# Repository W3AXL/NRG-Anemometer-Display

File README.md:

# NRG Anemometer Display
A compact, cheap interface unit for NRG #40C 3-cup anemometers.

This project started because I found a great deal on some NRG anemometers on eBay. Two for $40 was hard to turn down, especially because each unit is calibrated from the factory and said calibration is freely available on [NRG's website](https://www.nrgsystems.com/support/product-support/calibration-reports/).

The heavy lifting of the circuit was already done for me - the technical whitepaper from NRG clearly illustrates an almost-complete schematic. The only real work to be done was selection of components, the MCU interfacing, and board design for a nice compact meter.

I went through a lot of initial brainstorming for the interface concept - battery powered, or DC? Integrated data logging, or keep it simple? How many buttons? Should it beep at you annoyingly?

In the end, a dead-simple interface showing current and maximum wind readings was decided on. Power is provivded via a micro-USB plug, which also creates a serial port for real-time data transfer to a PC. The display is your standard run-of-the-mill eBay 1.3" OLED display, driven by I2C, and available for a few dollars all over the place. Boards were designed in Kicad and manufactured by JLCPCB. Components were sourced from Digikey, and the whole thing took a couple days to get working.

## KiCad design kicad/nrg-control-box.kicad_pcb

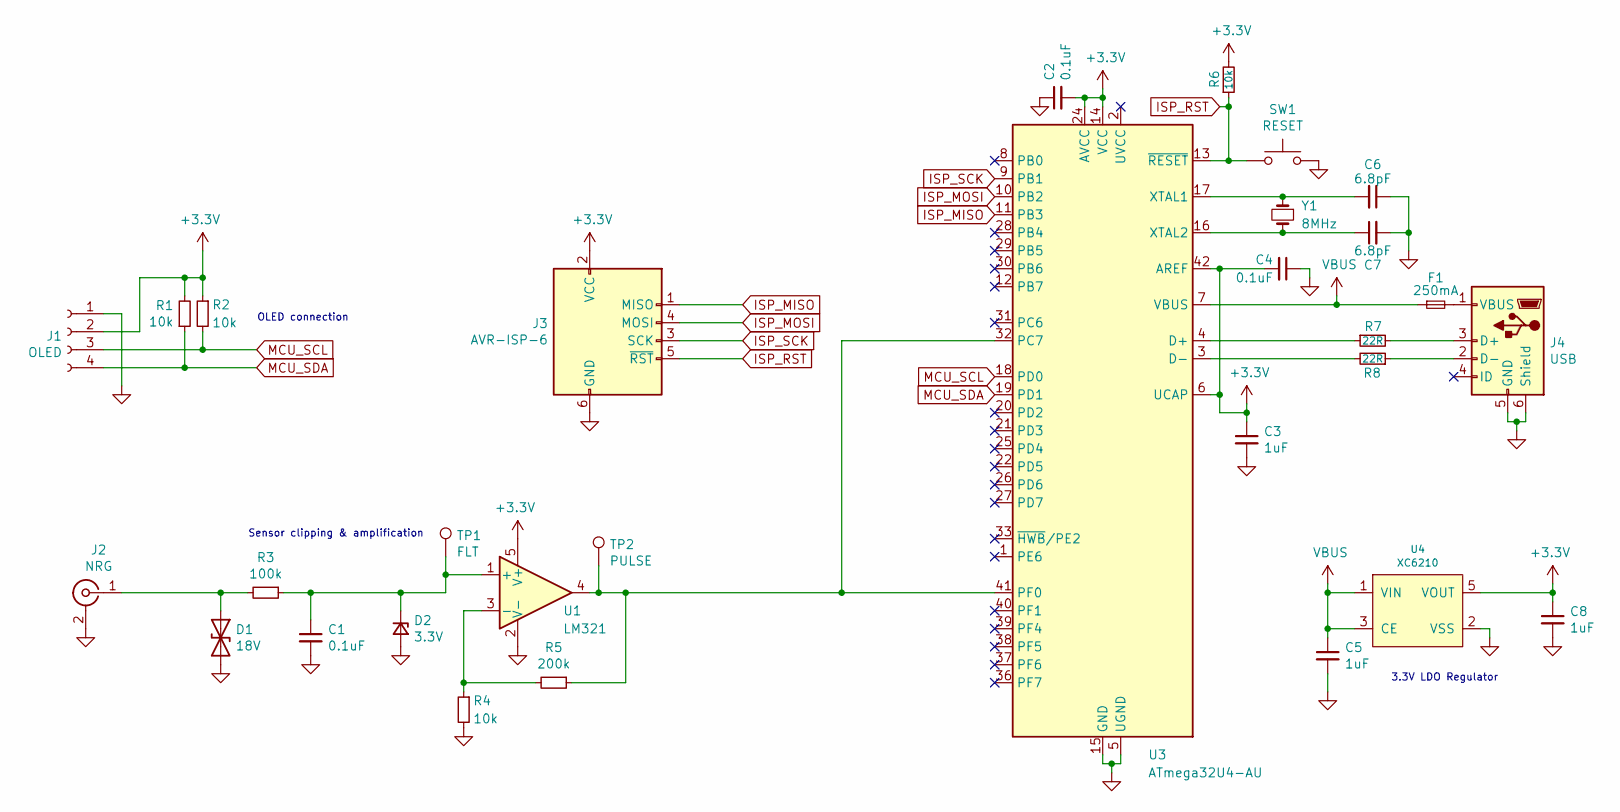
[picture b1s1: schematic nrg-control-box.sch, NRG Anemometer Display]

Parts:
C1, C2, C4: 0.1uF; C_0805_2012Metric_Pad1.15x1.40mm_HandSolder
C3, C5, C8: 1uF; C_0805_2012Metric_Pad1.15x1.40mm_HandSolder
C6, C7: 6.8pF; C_0805_2012Metric_Pad1.15x1.40mm_HandSolder
D1: 18V; D_SOD-323_HandSoldering
D2: 3.3V; D_SOD-323_HandSoldering
F1: 250mA; Fuse_1206_3216Metric_Pad1.42x1.75mm_HandSolder
J1: OLED; PinSocket_1x04_P2.54mm_Vertical
J2: NRG; RF3-04A-T-00-50-G
J3: AVR-ISP-6; PinSocket_1x06_P1.27mm_Vertical
J4: USB; 10118192-0001LF
R1, R2, R4, R6: 10k; R_0805_2012Metric_Pad1.15x1.40mm_HandSolder
R3: 100k; R_0805_2012Metric_Pad1.15x1.40mm_HandSolder
R5: 200k; R_0805_2012Metric_Pad1.15x1.40mm_HandSolder
R7, R8: 22R; R_0805_2012Metric_Pad1.15x1.40mm_HandSolder
SW1: RESET; SW_SPST_PTS645
TP1: FLT; TestPoint_Pad_1.0x1.0mm
TP2: PULSE; TestPoint_Pad_1.0x1.0mm
U1: LM321; SOT-23-5
U3: ATmega32U4-AU; TQFP-44_10x10mm_P0.8mm
U4: XC6210; SOT95P285X145-5N
Y1: 8MHz; NX8045GB

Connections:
+3V3: C2.2, C3.1, C4.2, C8.1, J1.2, J3.2 (VCC), R1.2, R2.1, R6.2, U1.5 (V+), U3.6 (UCAP), U3.14 (VCC), U3.24 (AVCC), U3.34 (VCC), U3.42 (AREF), U3.44 (AVCC), U4.5 (VOUT); also elsewhere on the board
GND: C1.2, C2.1, C3.2, C4.1, C5.2, C6.1, C7.2, C8.2, D1.2 (A2), D2.2 (A), J1.1, J2.2 (Ext), J3.6 (GND), J4.5 (GND), J4.6 (Shield), R4.2, SW1.2, U1.2 (V-), U3.5 (UGND), U3.15 (GND), U3.23 (GND), U3.35 (GND), U3.43 (GND), U4.2 (VSS); also elsewhere on the board
ISP_MISO: J3.1 (MISO), U3.11 (PB3)
ISP_MOSI: J3.4 (MOSI), U3.10 (PB2)
ISP_RST: J3.5 (~RST), R6.1, SW1.1, U3.13 (~RESET)
ISP_SCK: J3.3 (SCK), U3.9 (PB1)
MCU_SCL: J1.3, R2.2, U3.18 (PD0)
MCU_SDA: J1.4, R1.1, U3.19 (PD1)
unnamed: C1.1, D2.1 (K), R3.1, TP1.1, U1.1 (+)
unnamed: C6.2, U3.17 (XTAL1), Y1.1
unnamed: C7.1, U3.16 (XTAL2), Y1.2
unnamed: D1.1 (A1), J2.1 (In), R3.2
unnamed: F1.2, J4.1 (VBUS)
unnamed: J4.2 (D-), R8.1
unnamed: J4.3 (D+), R7.2
unnamed: R4.1, R5.2, U1.3 (-)
unnamed 17: R5.1, TP2.1, U1.4, U3.32 (PC7), U3.41 (PF0); also elsewhere on the board
unnamed: R7.1, U3.4 (D+)
unnamed: R8.2, U3.3 (D-)
VBUS: C5.1, F1.1, U3.7 (VBUS), U4.1 (VIN), U4.3 (CE)

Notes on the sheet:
Sensor clipping & amplification
OLED connection
3.3V LDO Regulator

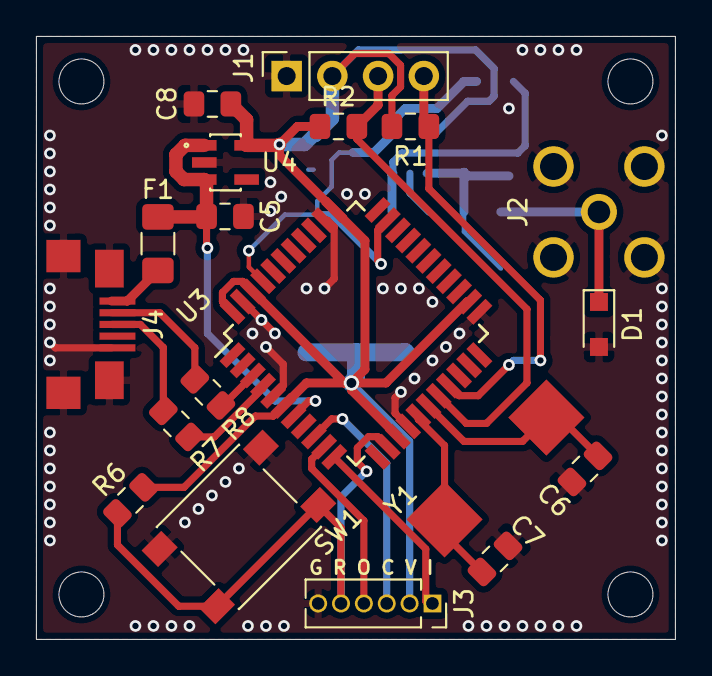
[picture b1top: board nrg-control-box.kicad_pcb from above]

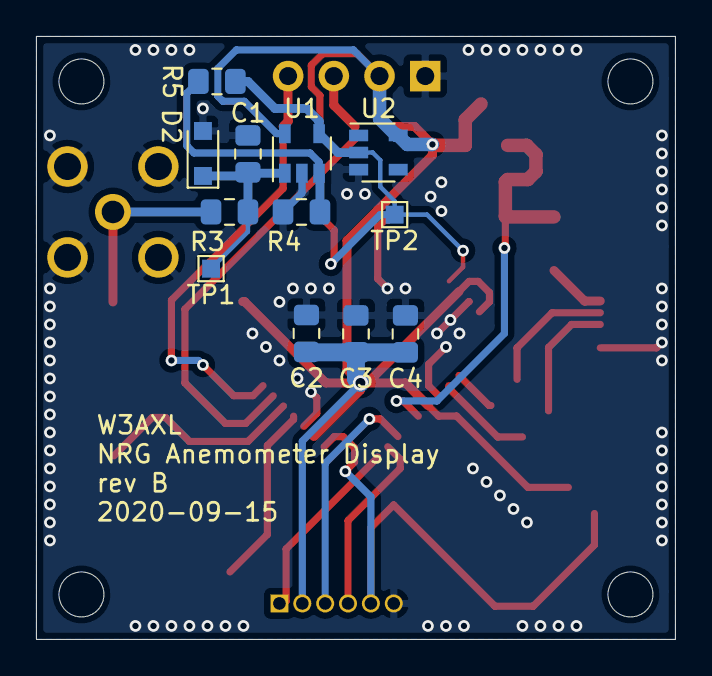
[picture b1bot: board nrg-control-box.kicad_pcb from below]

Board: 2 copper layers, 35.5 x 33.5 mm, 31 parts (12 on the bottom side), 20 nets.

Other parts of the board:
U2: SN74LVC1G14DBV; SOT-23-5

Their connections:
+3V3: U2.5; also elsewhere on the board
GND: U2.3; also elsewhere on the board
unnamed 17: U2.2; also elsewhere on the board

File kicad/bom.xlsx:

Ref | Qnty | Value | Cmp name | Footprint | Link | Description
C1, C2, C4, | 3 | 0.1uF | C_Small | C_0805 | Digikey | Unpolarized capacitor, small symbol
C3, C5, C8, | 3 | 1uF | C_Small | C_0805 | Digikey | Unpolarized capacitor, small symbol
C6, C7, | 2 | 6.8pF | C_Small | C_0805 | Digikey | Unpolarized capacitor, small symbol
D1, | 1 | 18V | D_TVS | SOD-323 | Digikey | Bidirectional transient-voltage-suppression diode
D2, | 1 | 3.3V | D_Zener_Small | SOD-323 | Digikey | Zener diode, small symbol
F1, | 1 | 250mA | Fuse_Small | F_1206 | Digikey | Polyfuse, 250mA hold current
J1, | 1 | OLED | Conn_01x04_Female | SMT 01x04 Female Recpt | Digikey | .180" Female Low Profile Socket, 0.1" Spacing
J2, | 1 | NRG | Conn_Coaxial | (Custom) Right Angle SMB Female Connector | Digikey | coaxial connector (BNC, SMA, SMB, SMC, Cinch/RCA, ...)
J3, | 1 | AVR-ISP-6 | AVR-ISP-6 | 1x6 0.1" Unsoldered Headers | n/a | Atmel 6-pin ISP connector
J4, | 1 | USB | USB_B_Micro | (Custom) Micro USB | Digikey | USB Micro Type B connector
R1, R2, R4, R6, | 4 | 10k | R_Small | R_0805 | Digikey | Resistor, small symbol
R3, R5 | 2 | 100k | R_Small | R_0805 | Digikey | Resistor, small symbol
R7, R8, | 2 | 22R | R_Small | R_0805 | Digikey | Resistor, small symbol
SW1, | 1 | RESET | SW_Push | PTS645 | Digikey | Push button switch, generic, two pins
U1, | 1 | LM321 | LM321 | SOT-23-5 | Digikey | Low Power Single Operational Amplifier, SOT-23-5
U2, | 1 | SN74LVC1G14DBV | SN74LVC1G14DBV | SOT-23-5 | Digikey | Single Schmitt-Trigger Inverter, SOT-23
U3, | 1 | ATmega32U4-AU | ATmega32U4-AU | TQFP-44 | Digikey | 16MHz, 32kB Flash, 2.5kB SRAM, 1kB EEPROM, USB 2.0, TQFP-44
U4, | 1 | XC6210B332MR-G | XC6210 | SOT-74A | Digikey | 3.3V LDO
Y1, | 1 | 8MHz | Crystal_Small | (Custom) SMD Crystal, 2-SMD | Digikey | Two pin crystal, small symbol

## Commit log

2020-09-15 initial github commit
    commit includes revision B of schematic and PCB, as well as version 0.1 of code
2020-09-17 switched from millis() to micros() for timing, simplified moving average
2020-09-18 added block diagram image from NRG whitepaper
2020-09-18 added block diagram
2020-09-19 added enclosure CAD files and media
2020-09-19 added cool pictures
2020-09-25 added basic outlier detection and increased screen refresh rate slightly
2020-10-16 changed outlier algorithm, added more detailed comments
2021-02-07 completed initial work on SW using FreqMeasure library. Required rewiring of board to pin PC7, will update in future SCH revision
2021-02-08 finalized code using FreqMeasure
    updated code to use Teensy FreqMeasure library listening on pin PC7. Still todo is schematic updates to reflect this change.
2021-02-08 updated schematic to reflect change in measurement pin to PC7
2021-02-08 removed g-code files
2023-09-11 added serial reporting and idle animation
